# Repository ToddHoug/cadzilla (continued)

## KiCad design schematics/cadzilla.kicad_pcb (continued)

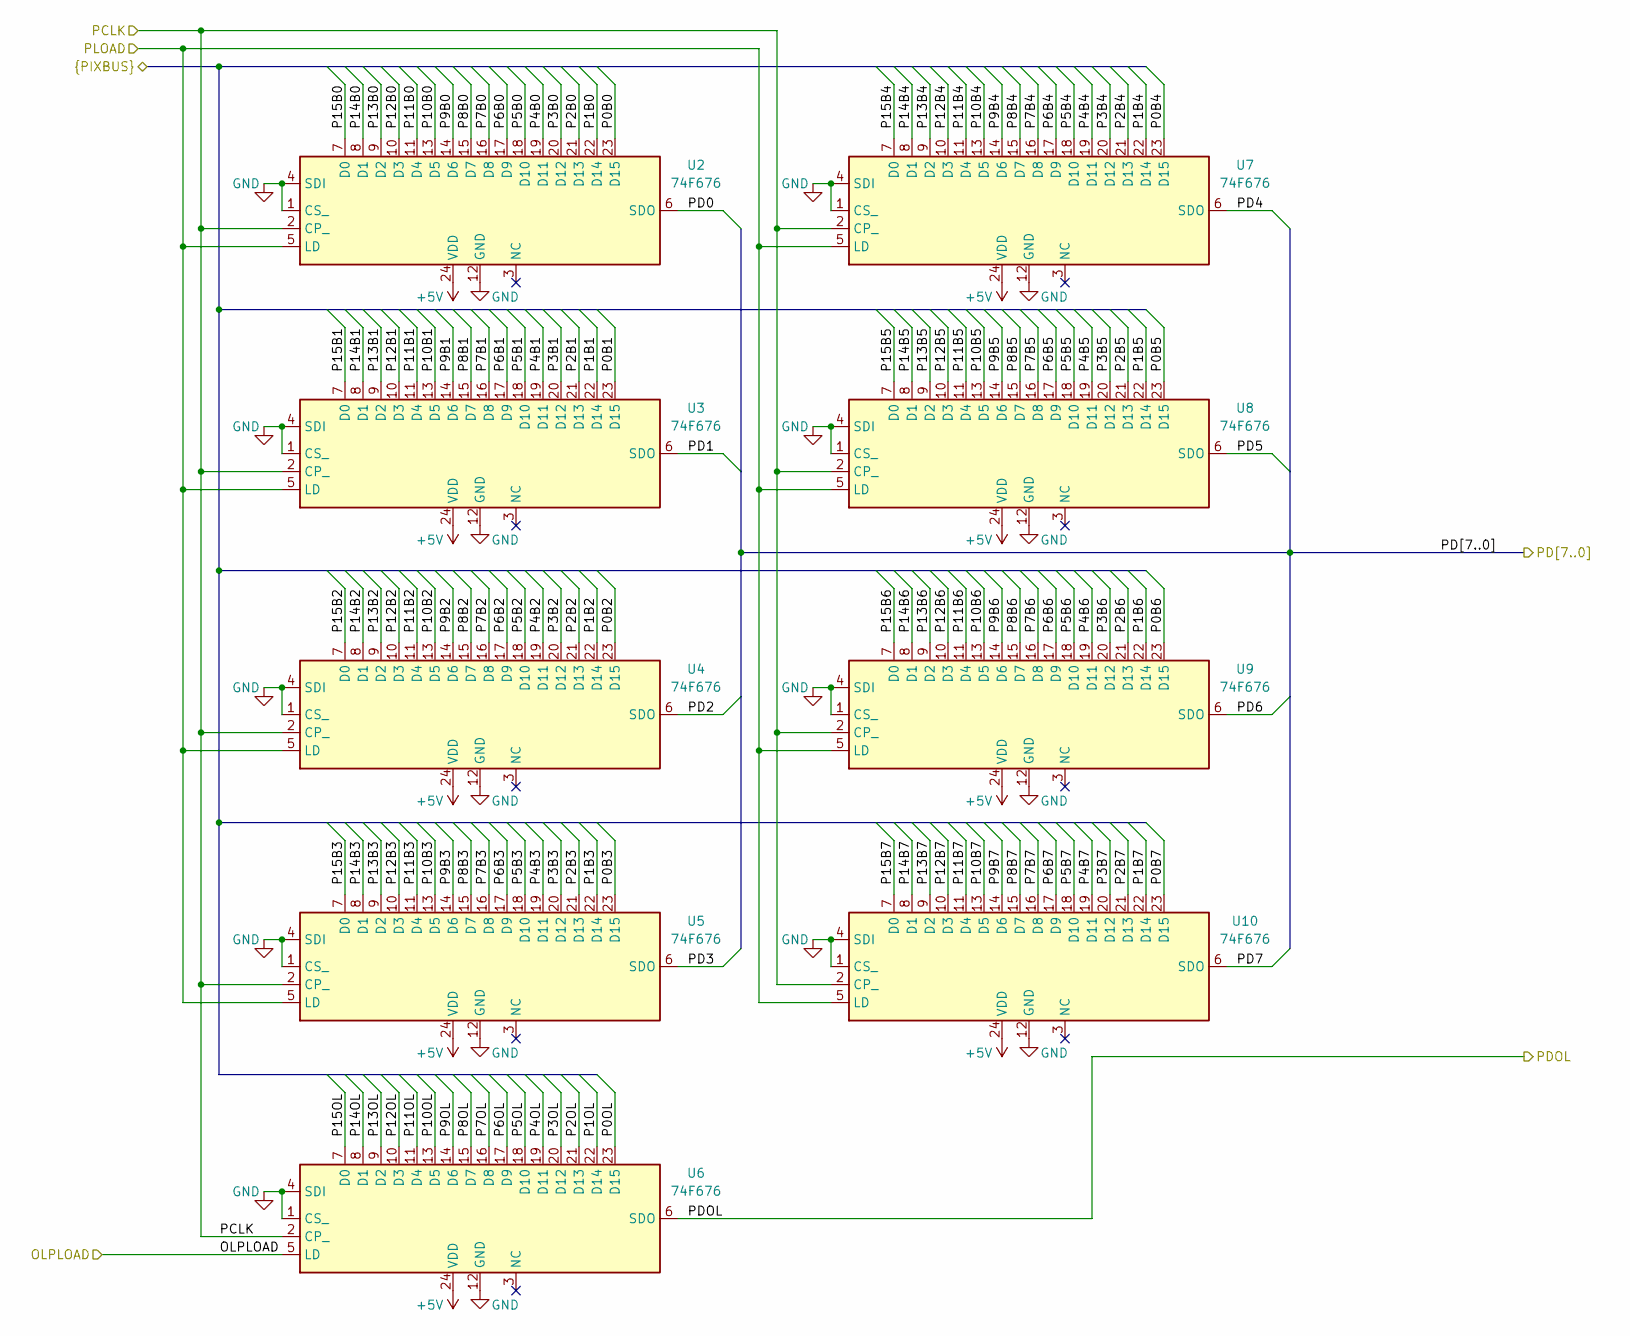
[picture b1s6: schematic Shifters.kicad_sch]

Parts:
U2, U3, U4, U5, U6, U7, U8, U9, U10: 74F676; DIP-24_W7.62mm_Socket_Small_Pads

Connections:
+5V: U2.24 (VDD), U3.24 (VDD), U4.24 (VDD), U5.24 (VDD), U6.24 (VDD), U7.24 (VDD), U8.24 (VDD), U9.24 (VDD), U10.24 (VDD); also elsewhere on the board
/Data Buffers/P0B0: U2.23 (D15); also elsewhere on the board
/Data Buffers/P0B1: U3.23 (D15); also elsewhere on the board
/Data Buffers/P0B2: U4.23 (D15); also elsewhere on the board
/Data Buffers/P0B3: U5.23 (D15); also elsewhere on the board
/Data Buffers/P0B4: U7.23 (D15); also elsewhere on the board
/Data Buffers/P0B5: U8.23 (D15); also elsewhere on the board
/Data Buffers/P0B6: U9.23 (D15); also elsewhere on the board
/Data Buffers/P0B7: U10.23 (D15); also elsewhere on the board
/Data Buffers/P0OL: U6.23 (D15); also elsewhere on the board
/Data Buffers/P1B0: U2.22 (D14); also elsewhere on the board
/Data Buffers/P1B1: U3.22 (D14); also elsewhere on the board
/Data Buffers/P1B2: U4.22 (D14); also elsewhere on the board
/Data Buffers/P1B3: U5.22 (D14); also elsewhere on the board
/Data Buffers/P1B4: U7.22 (D14); also elsewhere on the board
/Data Buffers/P1B5: U8.22 (D14); also elsewhere on the board
/Data Buffers/P1B6: U9.22 (D14); also elsewhere on the board
/Data Buffers/P1B7: U10.22 (D14); also elsewhere on the board
/Data Buffers/P1OL: U6.22 (D14); also elsewhere on the board
/Data Buffers/P2B0: U2.21 (D13); also elsewhere on the board
/Data Buffers/P2B1: U3.21 (D13); also elsewhere on the board
/Data Buffers/P2B2: U4.21 (D13); also elsewhere on the board
/Data Buffers/P2B3: U5.21 (D13); also elsewhere on the board
/Data Buffers/P2B4: U7.21 (D13); also elsewhere on the board
/Data Buffers/P2B5: U8.21 (D13); also elsewhere on the board
/Data Buffers/P2B6: U9.21 (D13); also elsewhere on the board
/Data Buffers/P2B7: U10.21 (D13); also elsewhere on the board
/Data Buffers/P2OL: U6.21 (D13); also elsewhere on the board
/Data Buffers/P3B0: U2.20 (D12); also elsewhere on the board
/Data Buffers/P3B1: U3.20 (D12); also elsewhere on the board
/Data Buffers/P3B2: U4.20 (D12); also elsewhere on the board
/Data Buffers/P3B3: U5.20 (D12); also elsewhere on the board
/Data Buffers/P3B4: U7.20 (D12); also elsewhere on the board
/Data Buffers/P3B5: U8.20 (D12); also elsewhere on the board
/Data Buffers/P3B6: U9.20 (D12); also elsewhere on the board
/Data Buffers/P3B7: U10.20 (D12); also elsewhere on the board
/Data Buffers/P3OL: U6.20 (D12); also elsewhere on the board
/Data Buffers/P4B0: U2.19 (D11); also elsewhere on the board
/Data Buffers/P4B1: U3.19 (D11); also elsewhere on the board
/Data Buffers/P4B2: U4.19 (D11); also elsewhere on the board
/Data Buffers/P4B3: U5.19 (D11); also elsewhere on the board
/Data Buffers/P4B4: U7.19 (D11); also elsewhere on the board
/Data Buffers/P4B5: U8.19 (D11); also elsewhere on the board
/Data Buffers/P4B6: U9.19 (D11); also elsewhere on the board
/Data Buffers/P4B7: U10.19 (D11); also elsewhere on the board
/Data Buffers/P4OL: U6.19 (D11); also elsewhere on the board
/Data Buffers/P5B0: U2.18 (D10); also elsewhere on the board
/Data Buffers/P5B1: U3.18 (D10); also elsewhere on the board
/Data Buffers/P5B2: U4.18 (D10); also elsewhere on the board
/Data Buffers/P5B3: U5.18 (D10); also elsewhere on the board
/Data Buffers/P5B4: U7.18 (D10); also elsewhere on the board
/Data Buffers/P5B5: U8.18 (D10); also elsewhere on the board
/Data Buffers/P5B6: U9.18 (D10); also elsewhere on the board
/Data Buffers/P5B7: U10.18 (D10); also elsewhere on the board
/Data Buffers/P5OL: U6.18 (D10); also elsewhere on the board
/Data Buffers/P6B0: U2.17 (D9); also elsewhere on the board
/Data Buffers/P6B1: U3.17 (D9); also elsewhere on the board
/Data Buffers/P6B2: U4.17 (D9); also elsewhere on the board
/Data Buffers/P6B3: U5.17 (D9); also elsewhere on the board
/Data Buffers/P6B4: U7.17 (D9); also elsewhere on the board
/Data Buffers/P6B5: U8.17 (D9); also elsewhere on the board
/Data Buffers/P6B6: U9.17 (D9); also elsewhere on the board
/Data Buffers/P6B7: U10.17 (D9); also elsewhere on the board
/Data Buffers/P6OL: U6.17 (D9); also elsewhere on the board
/Data Buffers/P7B0: U2.16 (D8); also elsewhere on the board
/Data Buffers/P7B1: U3.16 (D8); also elsewhere on the board
/Data Buffers/P7B2: U4.16 (D8); also elsewhere on the board
/Data Buffers/P7B3: U5.16 (D8); also elsewhere on the board
/Data Buffers/P7B4: U7.16 (D8); also elsewhere on the board
/Data Buffers/P7B5: U8.16 (D8); also elsewhere on the board
/Data Buffers/P7B6: U9.16 (D8); also elsewhere on the board
/Data Buffers/P7B7: U10.16 (D8); also elsewhere on the board
/Data Buffers/P7OL: U6.16 (D8); also elsewhere on the board
/Data Buffers/P8B0: U2.15 (D7); also elsewhere on the board
/Data Buffers/P8B1: U3.15 (D7); also elsewhere on the board
/Data Buffers/P8B2: U4.15 (D7); also elsewhere on the board
/Data Buffers/P8B3: U5.15 (D7); also elsewhere on the board
/Data Buffers/P8B4: U7.15 (D7); also elsewhere on the board
/Data Buffers/P8B5: U8.15 (D7); also elsewhere on the board
/Data Buffers/P8B6: U9.15 (D7); also elsewhere on the board
/Data Buffers/P8B7: U10.15 (D7); also elsewhere on the board
/Data Buffers/P8OL: U6.15 (D7); also elsewhere on the board
/Data Buffers/P9B0: U2.14 (D6); also elsewhere on the board
/Data Buffers/P9B1: U3.14 (D6); also elsewhere on the board
/Data Buffers/P9B2: U4.14 (D6); also elsewhere on the board
/Data Buffers/P9B3: U5.14 (D6); also elsewhere on the board
/Data Buffers/P9B4: U7.14 (D6); also elsewhere on the board
/Data Buffers/P9B5: U8.14 (D6); also elsewhere on the board
/Data Buffers/P9B6: U9.14 (D6); also elsewhere on the board
/Data Buffers/P9B7: U10.14 (D6); also elsewhere on the board
/Data Buffers/P9OL: U6.14 (D6); also elsewhere on the board
/Data Buffers/P10B0: U2.13 (D5); also elsewhere on the board
/Data Buffers/P10B1: U3.13 (D5); also elsewhere on the board
/Data Buffers/P10B2: U4.13 (D5); also elsewhere on the board
/Data Buffers/P10B3: U5.13 (D5); also elsewhere on the board
/Data Buffers/P10B4: U7.13 (D5); also elsewhere on the board
/Data Buffers/P10B5: U8.13 (D5); also elsewhere on the board
/Data Buffers/P10B6: U9.13 (D5); also elsewhere on the board
/Data Buffers/P10B7: U10.13 (D5); also elsewhere on the board
/Data Buffers/P10OL: U6.13 (D5); also elsewhere on the board
/Data Buffers/P11B0: U2.11 (D4); also elsewhere on the board
/Data Buffers/P11B1: U3.11 (D4); also elsewhere on the board
/Data Buffers/P11B2: U4.11 (D4); also elsewhere on the board
/Data Buffers/P11B3: U5.11 (D4); also elsewhere on the board
/Data Buffers/P11B4: U7.11 (D4); also elsewhere on the board
/Data Buffers/P11B5: U8.11 (D4); also elsewhere on the board
/Data Buffers/P11B6: U9.11 (D4); also elsewhere on the board
/Data Buffers/P11B7: U10.11 (D4); also elsewhere on the board
/Data Buffers/P11OL: U6.11 (D4); also elsewhere on the board
/Data Buffers/P12B0: U2.10 (D3); also elsewhere on the board
/Data Buffers/P12B1: U3.10 (D3); also elsewhere on the board
/Data Buffers/P12B2: U4.10 (D3); also elsewhere on the board
/Data Buffers/P12B3: U5.10 (D3); also elsewhere on the board
/Data Buffers/P12B4: U7.10 (D3); also elsewhere on the board
/Data Buffers/P12B5: U8.10 (D3); also elsewhere on the board
/Data Buffers/P12B6: U9.10 (D3); also elsewhere on the board
/Data Buffers/P12B7: U10.10 (D3); also elsewhere on the board
/Data Buffers/P12OL: U6.10 (D3); also elsewhere on the board
/Data Buffers/P13B0: U2.9 (D2); also elsewhere on the board
/Data Buffers/P13B1: U3.9 (D2); also elsewhere on the board
/Data Buffers/P13B2: U4.9 (D2); also elsewhere on the board
/Data Buffers/P13B3: U5.9 (D2); also elsewhere on the board
/Data Buffers/P13B4: U7.9 (D2); also elsewhere on the board
/Data Buffers/P13B5: U8.9 (D2); also elsewhere on the board
/Data Buffers/P13B6: U9.9 (D2); also elsewhere on the board
/Data Buffers/P13B7: U10.9 (D2); also elsewhere on the board
/Data Buffers/P13OL: U6.9 (D2); also elsewhere on the board
/Data Buffers/P14B0: U2.8 (D1); also elsewhere on the board
/Data Buffers/P14B1: U3.8 (D1); also elsewhere on the board
/Data Buffers/P14B2: U4.8 (D1); also elsewhere on the board
/Data Buffers/P14B3: U5.8 (D1); also elsewhere on the board
/Data Buffers/P14B4: U7.8 (D1); also elsewhere on the board
/Data Buffers/P14B5: U8.8 (D1); also elsewhere on the board
/Data Buffers/P14B6: U9.8 (D1); also elsewhere on the board
/Data Buffers/P14B7: U10.8 (D1); also elsewhere on the board
/Data Buffers/P14OL: U6.8 (D1); also elsewhere on the board
/Data Buffers/P15B0: U2.7 (D0); also elsewhere on the board
/Data Buffers/P15B1: U3.7 (D0); also elsewhere on the board
/Data Buffers/P15B2: U4.7 (D0); also elsewhere on the board
/Data Buffers/P15B3: U5.7 (D0); also elsewhere on the board
/Data Buffers/P15B4: U7.7 (D0); also elsewhere on the board
/Data Buffers/P15B5: U8.7 (D0); also elsewhere on the board
/Data Buffers/P15B6: U9.7 (D0); also elsewhere on the board
/Data Buffers/P15B7: U10.7 (D0); also elsewhere on the board
/Data Buffers/P15OL: U6.7 (D0); also elsewhere on the board
/Shift Registers/OLPLOAD: U6.5 (LD); also elsewhere on the board
/Shift Registers/PCLK: U2.2 (CP_), U3.2 (CP_), U4.2 (CP_), U5.2 (CP_), U6.2 (CP_), U7.2 (CP_), U8.2 (CP_), U9.2 (CP_), U10.2 (CP_); also elsewhere on the board
/Shift Registers/PD0: U2.6 (SDO); also elsewhere on the board
/Shift Registers/PD1: U3.6 (SDO); also elsewhere on the board
/Shift Registers/PD2: U4.6 (SDO); also elsewhere on the board
/Shift Registers/PD3: U5.6 (SDO); also elsewhere on the board
/Shift Registers/PD4: U7.6 (SDO); also elsewhere on the board
/Shift Registers/PD5: U8.6 (SDO); also elsewhere on the board
/Shift Registers/PD6: U9.6 (SDO); also elsewhere on the board
/Shift Registers/PD7: U10.6 (SDO); also elsewhere on the board
/Shift Registers/PDOL: U6.6 (SDO); also elsewhere on the board
/Shift Registers/PLOAD: U2.5 (LD), U3.5 (LD), U4.5 (LD), U5.5 (LD), U7.5 (LD), U8.5 (LD), U9.5 (LD), U10.5 (LD); also elsewhere on the board
GND: U2.1 (CS_), U2.4 (SDI), U2.12 (GND), U3.1 (CS_), U3.4 (SDI), U3.12 (GND), U4.1 (CS_), U4.4 (SDI), U4.12 (GND), U5.1 (CS_), U5.4 (SDI), U5.12 (GND), U6.1 (CS_), U6.4 (SDI), U6.12 (GND), U7.1 (CS_), U7.4 (SDI), U7.12 (GND), U8.1 (CS_), U8.4 (SDI), U8.12 (GND), U9.1 (CS_), U9.4 (SDI), U9.12 (GND), U10.1 (CS_), U10.4 (SDI), U10.12 (GND); also elsewhere on the board

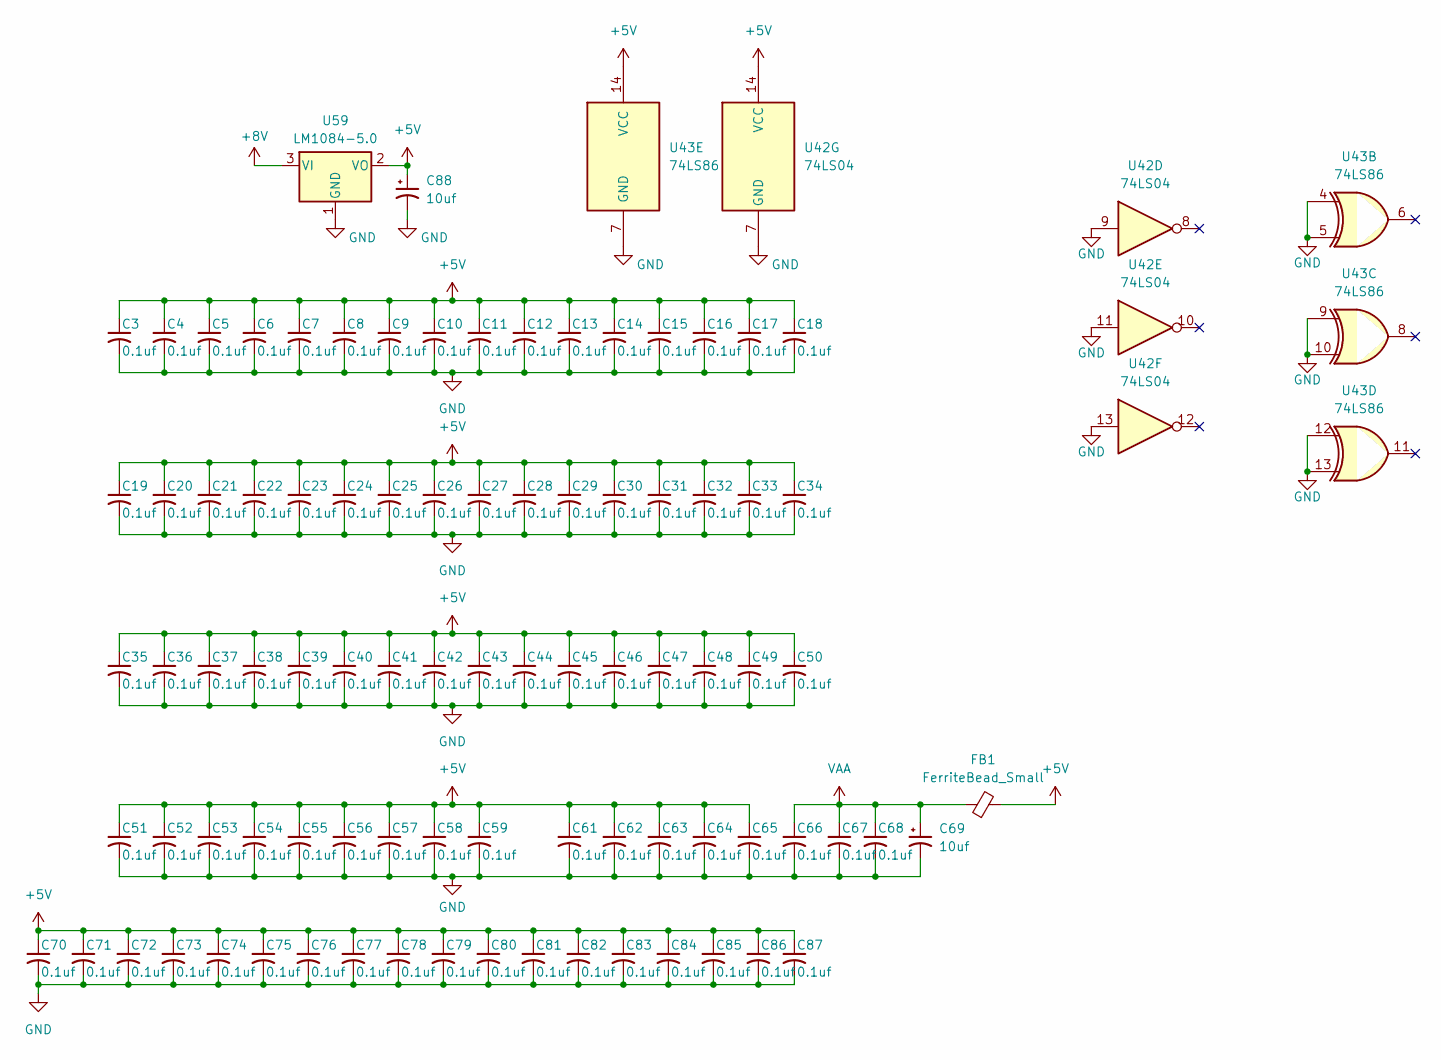
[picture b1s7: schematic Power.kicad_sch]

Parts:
C3, C4, C5, C6, C7, C10, C11, C12, C13, C14, C17, C18, C19, C20, C21, C26, C27, C28, C29, C30, C33, C34, C35, C36, C37, C40, C41, C42, C43, C44, C46, C47, C48, C49, C50, C53, C54, C55, C56, C57, C59, C62, C63, C64, C65: 0.1uf; C_Rect_L9.1mm_W2.5mm_P7.62mm_MKT
C8, C9, C15, C16, C22, C23, C24, C25, C31, C32, C38, C39, C45, C51, C52, C58, C61: 0.1uf; C_Rect_L9.1mm_W2.5mm_P7.62mm_Small_Pads
C66, C67, C68: 0.1uf; C_0805_2012Metric_Pad1.18x1.45mm_HandSolder
C69, C88: 10uf; C_Rect_L9.1mm_W2.5mm_P7.62mm_MKT
C70, C71, C72, C73, C74, C75, C76, C77, C78, C79, C80, C81, C82, C83, C84, C85, C86, C87: 0.1uf; C_0603_1608Metric_Pad1.08x0.95mm_HandSolder
FB1: FerriteBead_Small; C_Rect_L9.1mm_W2.5mm_P7.62mm_MKT
U42: 74LS04; DIP-14_W7.62mm_Socket
U43: 74LS86; DIP-14_W7.62mm_Socket
U59: LM1084-5.0; TO-220F-3_Horizontal_TabDown

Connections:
+5V: C3.1, C4.1, C5.1, C6.1, C7.1, C8.1, C9.1, C10.1, C11.1, C12.1, C13.1, C14.1, C15.1, C16.1, C17.1, C18.1, C19.1, C20.1, C21.1, C22.1, C23.1, C24.1, C25.1, C26.1, C27.1, C28.1, C29.1, C30.1, C31.1, C32.1, C33.1, C34.1, C35.1, C36.1, C37.1, C38.1, C39.1, C40.1, C41.1, C42.1, C43.1, C44.1, C45.1, C46.1, C47.1, C48.1, C49.1, C50.1, C51.1, C52.1, C53.1, C54.1, C55.1, C56.1, C57.1, C58.1, C59.1, C61.1, C62.1, C63.1, C64.1, C65.1, C70.1, C71.1, C72.1, C73.1, C74.1, C75.1, C76.1, C77.1, C78.1, C79.1, C80.1, C81.1, C82.1, C83.1, C84.1, C85.1, C86.1, C87.1, C88.1, FB1.2, U42.14 (VCC), U43.14 (VCC), U59.2 (VO); also elsewhere on the board
+8V: U59.3 (VI); also elsewhere on the board
GND: C3.2, C4.2, C5.2, C6.2, C7.2, C8.2, C9.2, C10.2, C11.2, C12.2, C13.2, C14.2, C15.2, C16.2, C17.2, C18.2, C19.2, C20.2, C21.2, C22.2, C23.2, C24.2, C25.2, C26.2, C27.2, C28.2, C29.2, C30.2, C31.2, C32.2, C33.2, C34.2, C35.2, C36.2, C37.2, C38.2, C39.2, C40.2, C41.2, C42.2, C43.2, C44.2, C45.2, C46.2, C47.2, C48.2, C49.2, C50.2, C51.2, C52.2, C53.2, C54.2, C55.2, C56.2, C57.2, C58.2, C59.2, C61.2, C62.2, C63.2, C64.2, C65.2, C66.2, C67.2, C68.2, C69.2, C70.2, C71.2, C72.2, C73.2, C74.2, C75.2, C76.2, C77.2, C78.2, C79.2, C80.2, C81.2, C82.2, C83.2, C84.2, C85.2, C86.2, C87.2, C88.2, U42.7 (GND), U42.9, U42.11, U42.13, U43.4, U43.5, U43.7 (GND), U43.9, U43.10, U43.12, U43.13, U59.1 (GND); also elsewhere on the board
VAA: C66.1, C67.1, C68.1, C69.1, FB1.1; also elsewhere on the board
